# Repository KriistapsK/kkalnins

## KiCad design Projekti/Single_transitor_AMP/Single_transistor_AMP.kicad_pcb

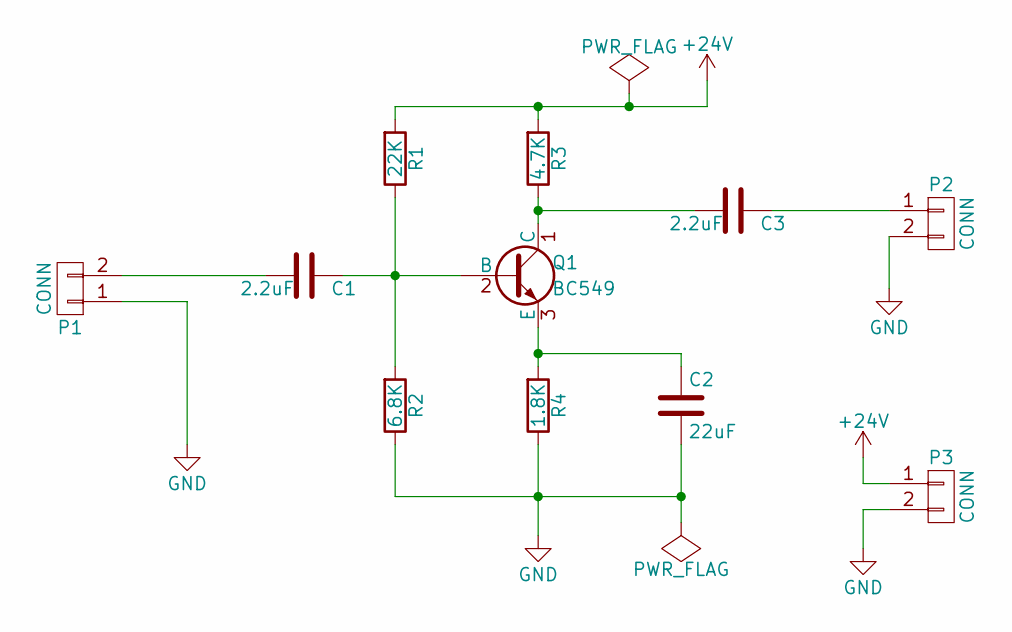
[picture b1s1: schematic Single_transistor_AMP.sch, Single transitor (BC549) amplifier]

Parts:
C1, C3: 2.2uF; CP_Radial_D10.0mm_P2.50mm
C2: 22uF; CP_Radial_D10.0mm_P2.50mm
P1, P2, P3: CONN; AK300-2
Q1: BC549; TO-92_Inline_Wide
R1: 22K; R_Axial_DIN0309_L9.0mm_D3.2mm_P15.24mm_Horizontal
R2: 6.8K; R_Axial_DIN0309_L9.0mm_D3.2mm_P15.24mm_Horizontal
R3: 4.7K; R_Axial_DIN0309_L9.0mm_D3.2mm_P15.24mm_Horizontal
R4: 1.8K; R_Axial_DIN0309_L9.0mm_D3.2mm_P15.24mm_Horizontal

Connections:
+24V: P3.1, R1.2, R3.2
GND: C2.2, P1.1, P2.2, P3.2, R2.1, R4.1
unnamed: C1.1, Q1.2 (B), R1.1, R2.2
unnamed: C1.2, P1.2
unnamed: C2.1, Q1.3 (E), R4.2
unnamed: C3.1, P2.1
unnamed: C3.2, Q1.1 (C), R3.1

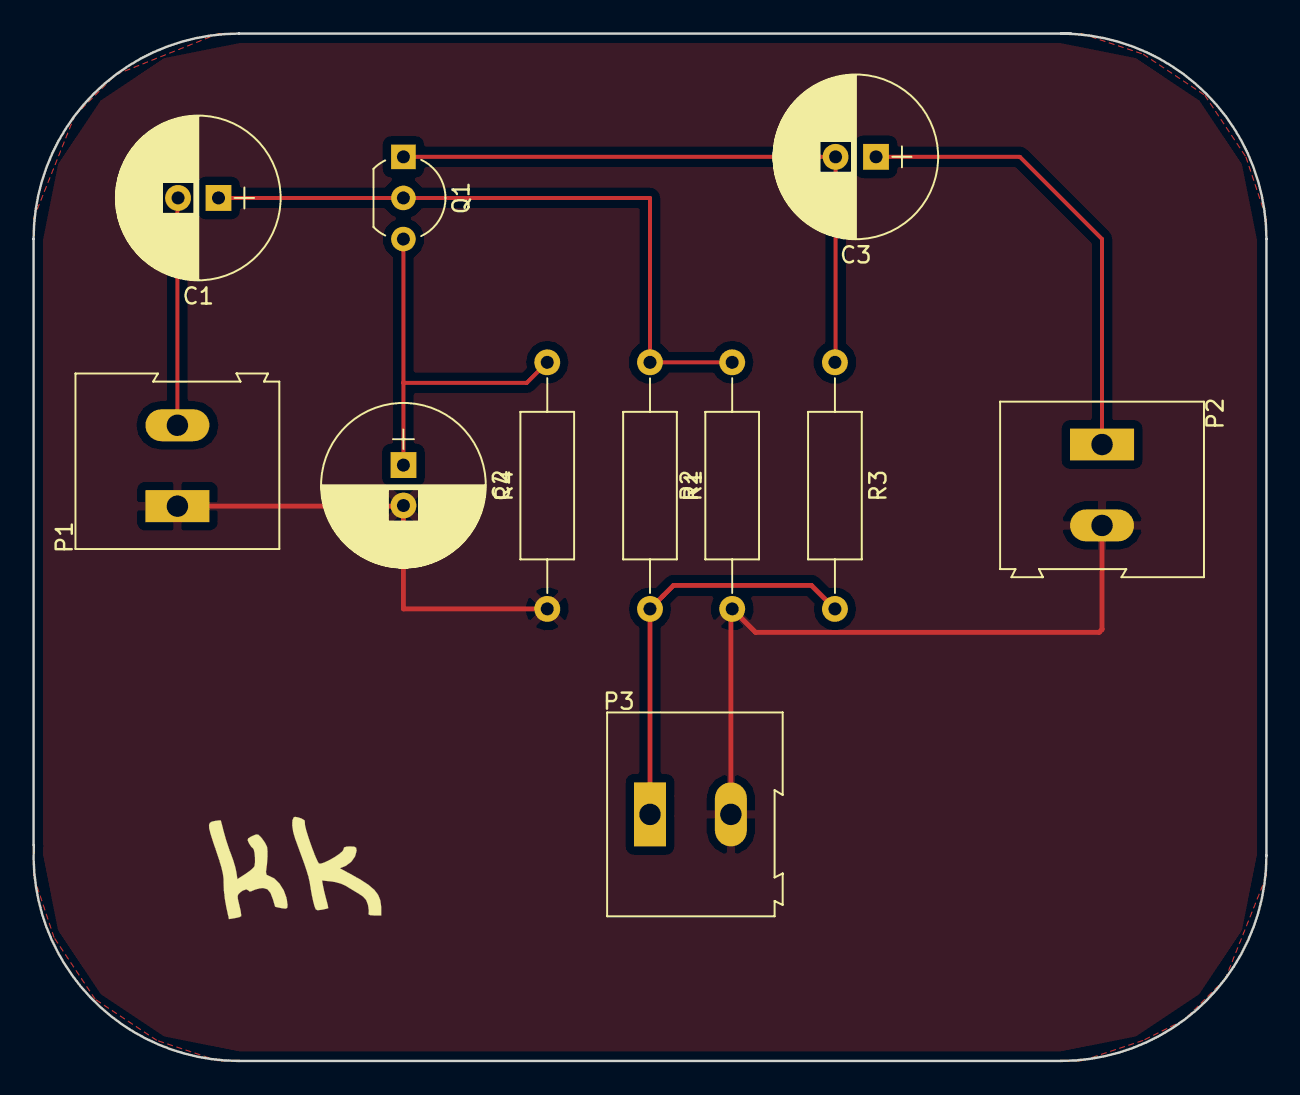
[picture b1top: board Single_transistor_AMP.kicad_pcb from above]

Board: 2 copper layers, 76.2 x 63.5 mm, 11 parts (0 on the bottom side), 7 nets.

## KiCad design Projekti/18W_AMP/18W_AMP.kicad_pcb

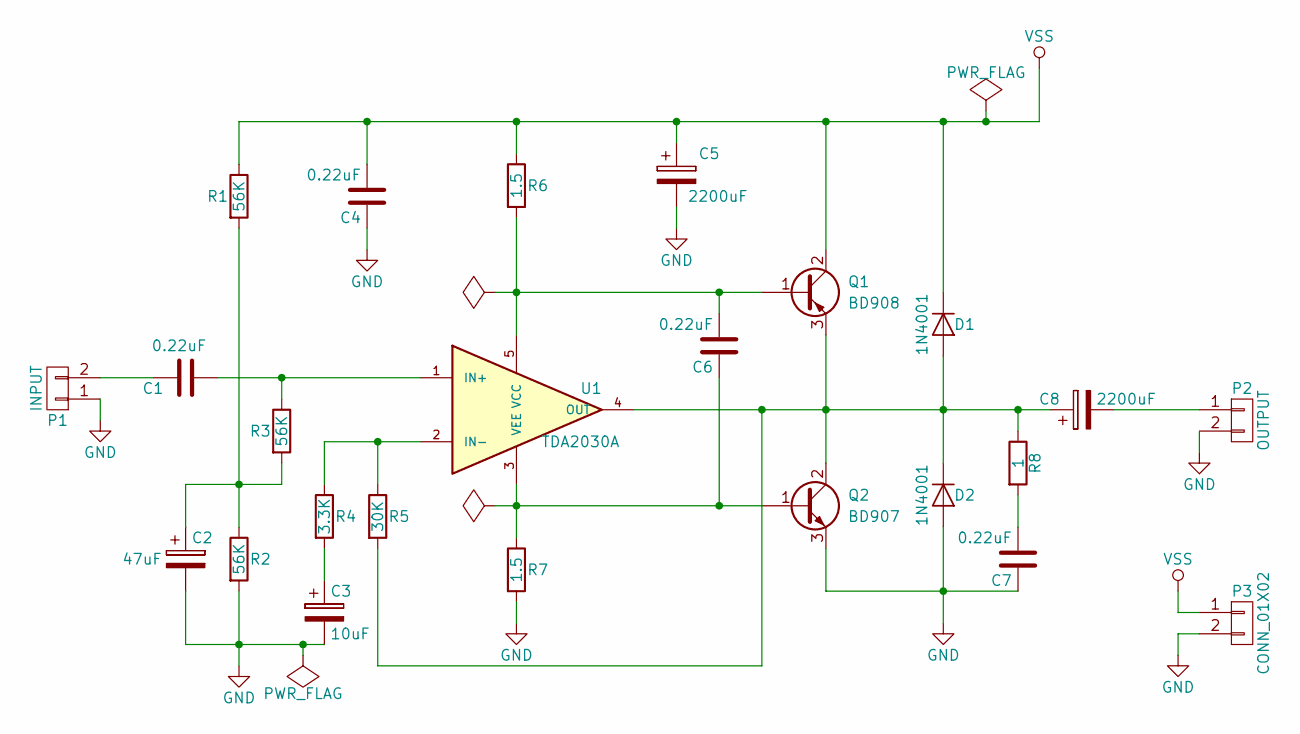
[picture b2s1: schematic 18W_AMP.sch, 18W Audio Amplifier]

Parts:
C1, C4, C6, C7: 0.22uF; C_Axial_L17.0mm_D6.5mm_P20.00mm_Horizontal
C2: 47uF; CP_Radial_D6.3mm_P2.50mm
C3: 10uF; CP_Radial_D4.0mm_P1.50mm
C5, C8: 2200uF; CP_Radial_D18.0mm_P7.50mm
D1, D2: 1N4001; D_A-405_P10.16mm_Horizontal
P1: INPUT; AK300-2
P2: OUTPUT; AK300-2
P3: CONN_01X02; AK300-2
Q1: BD908; TO-220-4_Horizontal
Q2: BD907; TO-220-4_Horizontal
R1, R2, R3: 56K; R_Axial_DIN0516_L15.5mm_D5.0mm_P25.40mm_Horizontal
R4: 3.3K; R_Axial_DIN0411_L9.9mm_D3.6mm_P20.32mm_Horizontal
R5: 30K; R_Axial_DIN0414_L11.9mm_D4.5mm_P20.32mm_Horizontal
R6, R7: 1.5; R_Axial_DIN0204_L3.6mm_D1.6mm_P7.62mm_Horizontal
R8: 1; R_Axial_DIN0204_L3.6mm_D1.6mm_P7.62mm_Horizontal
U1: TDA2030A; TO-220-5_Pentawatt_Multiwatt-5_Horizontal_StaggeredType2

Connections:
GND: C2.2, C3.2, C4.1, C5.2, C7.1, D2.2 (A), P1.1, P2.2, P3.2, Q2.3 (E), R2.2, R7.2
unnamed: C1.1, P1.2
unnamed: C1.2, R3.1, U1.1 (IN+)
unnamed: C2.1, R1.2, R2.1, R3.2
unnamed: C3.1, R4.2
unnamed: C6.1, Q2.1 (B), R7.1, U1.3 (VEE)
unnamed: C6.2, Q1.1 (B), R6.2, U1.5 (VCC)
unnamed: C7.2, R8.2
unnamed: C8.1, D1.2 (A), D2.1 (K), Q1.3 (E), Q2.2 (C), R5.2, R8.1, U1.4 (OUT)
unnamed: C8.2, P2.1
unnamed: R4.1, R5.1, U1.2 (IN-)
VSS: C4.2, C5.1, D1.1 (K), P3.1, Q1.2 (C), R1.1, R6.1

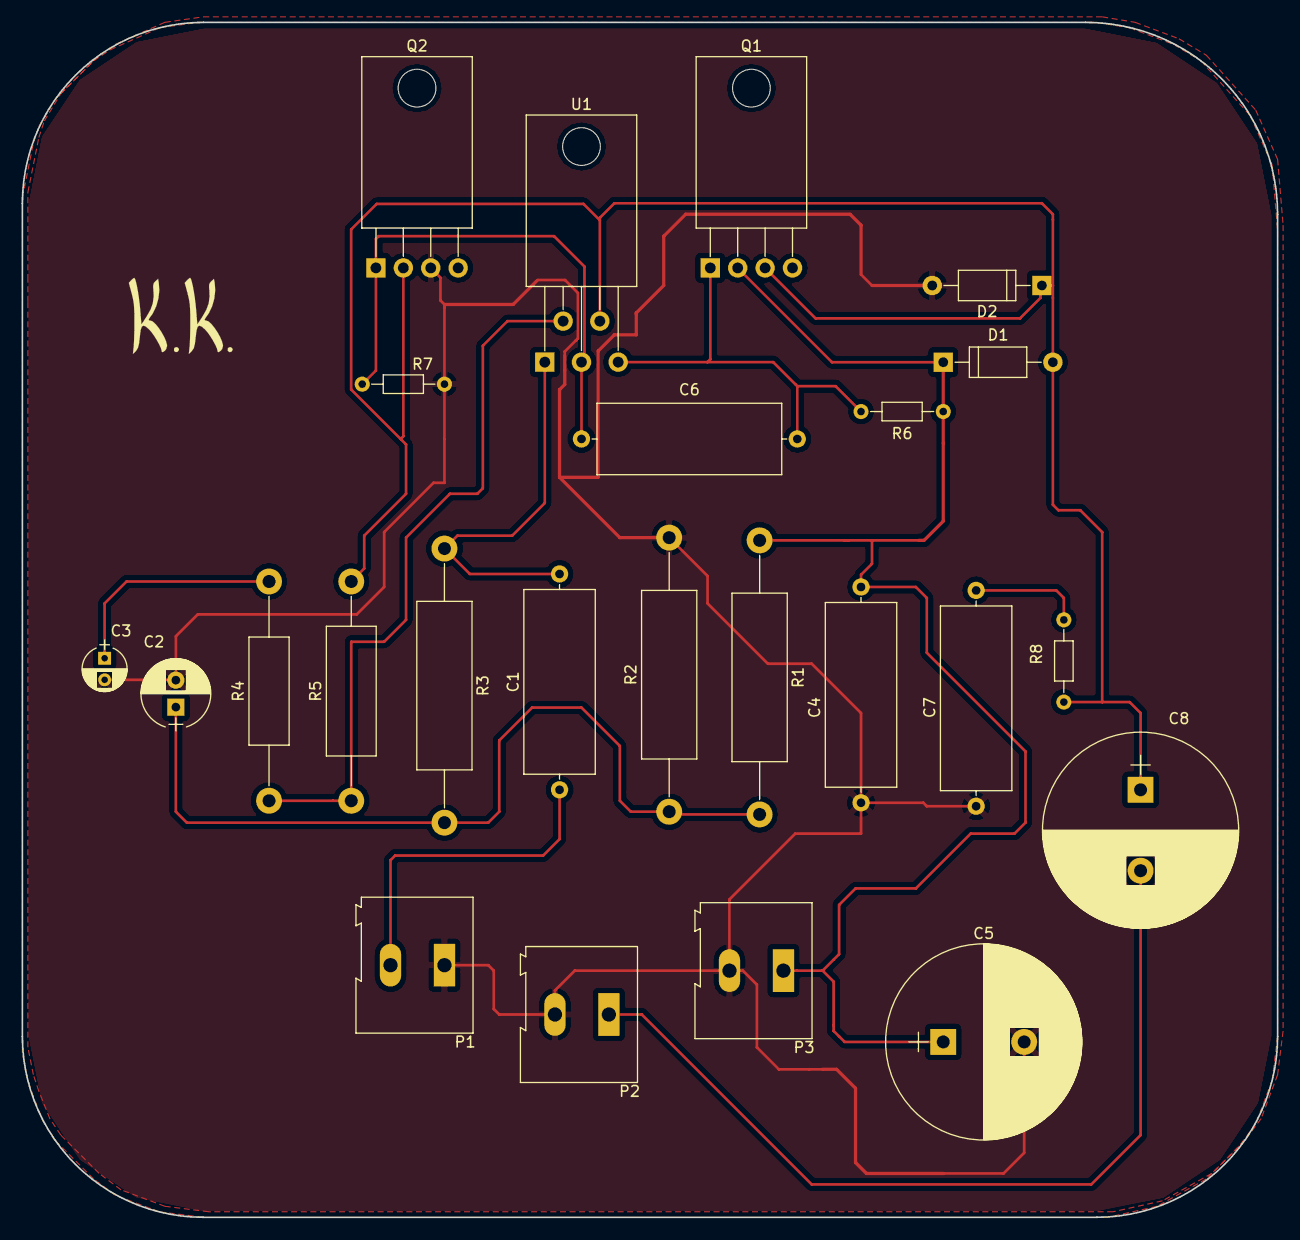
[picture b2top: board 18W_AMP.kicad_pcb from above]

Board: 2 copper layers, 116.3 x 110.7 mm, 24 parts (0 on the bottom side), 12 nets.

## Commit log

2017-03-02 README update
2017-03-08 izdaraam 1. izmainas
2017-03-08 veicam 2. izmainas
2017-03-09 Projekta sakums
2017-03-09 pabeigts projekts Multivib
2017-03-09 pievienojaam lib jaunu kompunenti
2017-03-14 Otrais MD ar aizvietotu IC komponenti
2017-03-22 daljeeji pabeigts 2md
2017-03-22 Savienojaam pin's
2017-03-23 pievienojam biblioteku relative path
2017-03-23 uzzimejam shemu ampam
2017-03-23 Single transitor amp
2017-03-23 sheema 3. md
2017-03-27 Pabeigts 3rd majasdarbs
2017-03-30 pabeigts lekcijas darbs
2017-04-18 pabeigts md ar bateriju turetajiem
2017-05-11 pebeigts md par layout
2017-05-18 tika izstradata traseshana un izvedoti gerber faili
2017-05-18 gbr faili
2017-05-28 BOM un .svg faili; 1/2 pabeigts kursa darbs
2017-05-29 pedejas izmainas
2017-05-29 principā pabeigts kursa darbs, vēl daži sīkumi
2017-05-30 Pabeigts kursa darbs
2017-06-16 izmainas
